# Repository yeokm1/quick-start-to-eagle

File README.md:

# quick-start-to-eagle
A talk I gave at [Hackware v1.7](https://www.facebook.com/events/180525638991544/) about introducing people to the basics of using Eagle.

##Video of this talk

My slides are available on slideshare using the picture link below.

The content of this talk is a [reduced version of a completed class](https://github.com/yeokm1/intro-to-pcb-design-eagle) I gave before.

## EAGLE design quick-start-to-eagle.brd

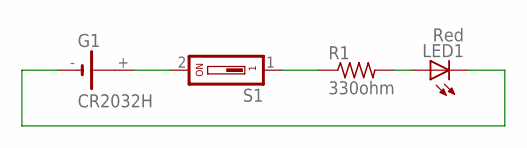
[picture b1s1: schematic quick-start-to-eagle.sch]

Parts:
G1: CR2032H
LED1: Red; LED5MM
R1: 330ohm; 0207/10
S1: SD4-01

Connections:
unnamed: G1.+, S1.2
unnamed: R1.1, S1.1
unnamed: LED1.A, R1.2
unnamed: G1.-, LED1.K (C)

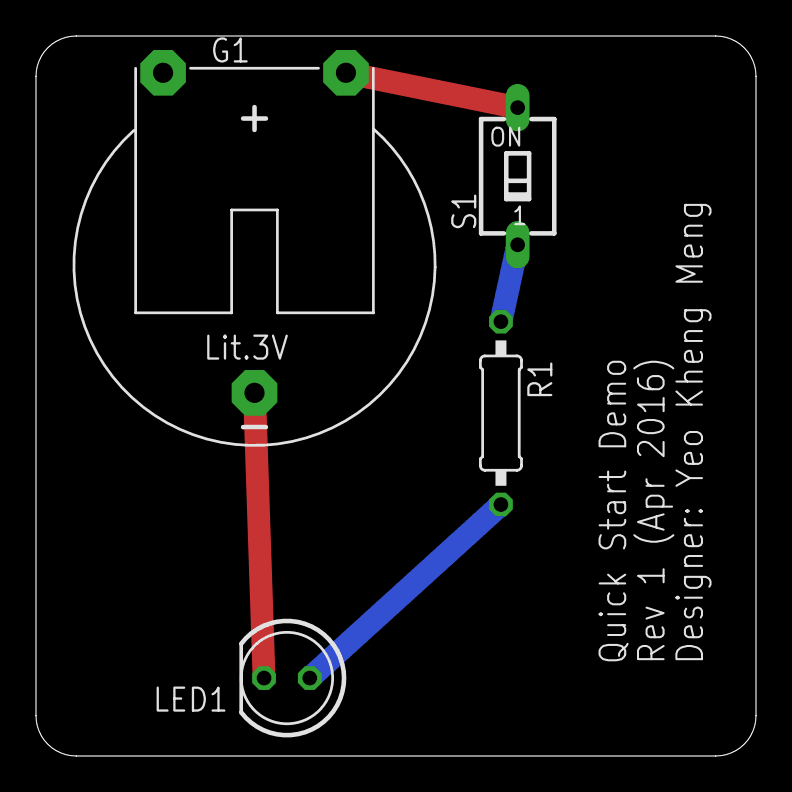
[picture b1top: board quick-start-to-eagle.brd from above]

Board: 2 copper layers, 40.0 x 40.0 mm, 4 parts (0 on the bottom side), 4 nets.

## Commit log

2016-04-17 first slide image
2016-04-17 adjust first slide
2016-04-26 open in windowed mode
